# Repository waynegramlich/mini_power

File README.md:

mini_power
==========

Mini-Shield for Power

There is a nifty
[YouTube video](https://www.youtube.com/watch?v=IrB-FPcv1Dc)
that explains how a P-channel MOSFET polarity protection cirucit
works.

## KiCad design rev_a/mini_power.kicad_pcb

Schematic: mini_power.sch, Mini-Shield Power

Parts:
G1: OSHW_LOGO
H1: 3MM_HOLE
N1: MS_DATA_HEADER_POWER
N2: MS_PWR_HEADER_POWER
N3, N4, N5, N6, N7: OSTTC020162
Q1, Q2: FQP47P06
R1: MF-R300
R2: RESETABLE_FUSE
SW1: F-426-0020

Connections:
/GND: H1.1, N2.5, N2.6, N6.1 (-), N7.1 (-), Q2.G
/LPWR1: N6.2 (+), N7.2 (+), Q2.D
/LPWR2: Q2.S, R2.1
/LPWR3: R2.2, SW1.4
/LPWR4: N3.2, N4.2 (+), N5.2 (+)
/MGND: N2.15, N2.16, N4.1 (-), N5.1 (-), Q1.G
/MPWR: N1.15, N1.16, SW1.2
/MPWR1: N3.1, Q1.D
/MPWR2: Q1.S, R1.1
/MPWR3: R1.2, SW1.1
/VIN: N2.1, N2.2, SW1.5

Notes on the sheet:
Daisy Chain Motor Power
Motor Emergency Stop
Logic Power Daisy Chain

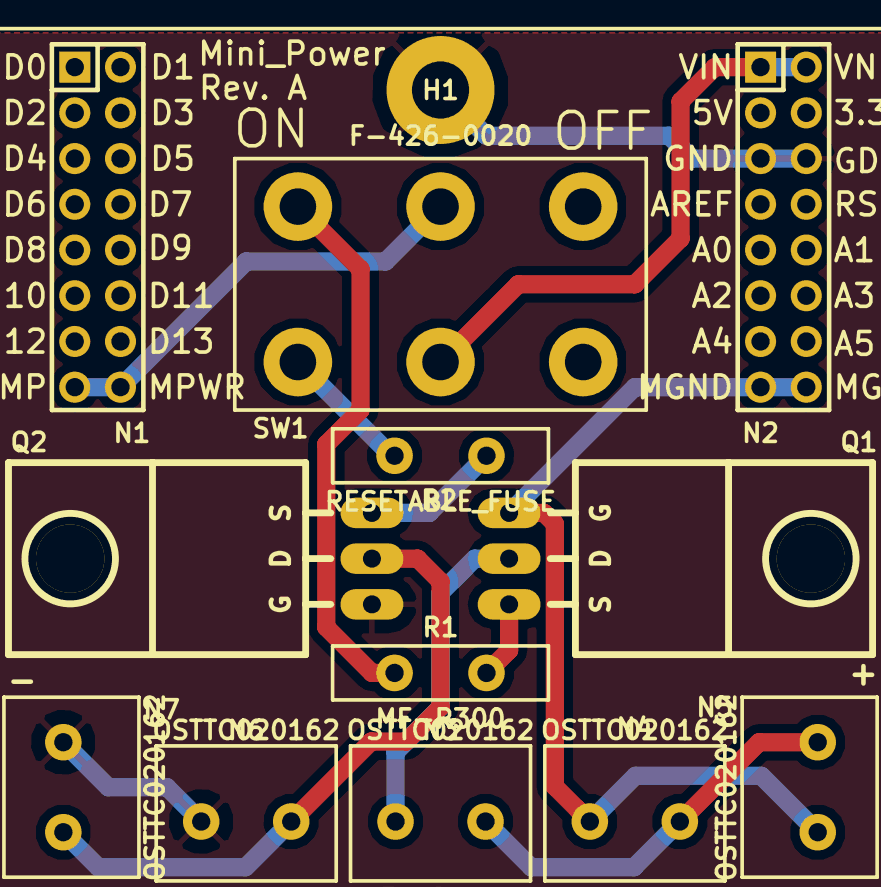
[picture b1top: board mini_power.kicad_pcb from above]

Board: 2 copper layers, 14 parts (1 on the bottom side), 11 nets.

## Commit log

2014-07-04 Initial copy from mini_template.
2014-07-04 Did initial schematic for power mini-shield.
2014-07-05 Did initial board layout.
2014-07-13 Added Edge Cuts.

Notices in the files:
rev_a/mini_power.kicad_pcb:
Copyright (c) 2014 - Gramlich
